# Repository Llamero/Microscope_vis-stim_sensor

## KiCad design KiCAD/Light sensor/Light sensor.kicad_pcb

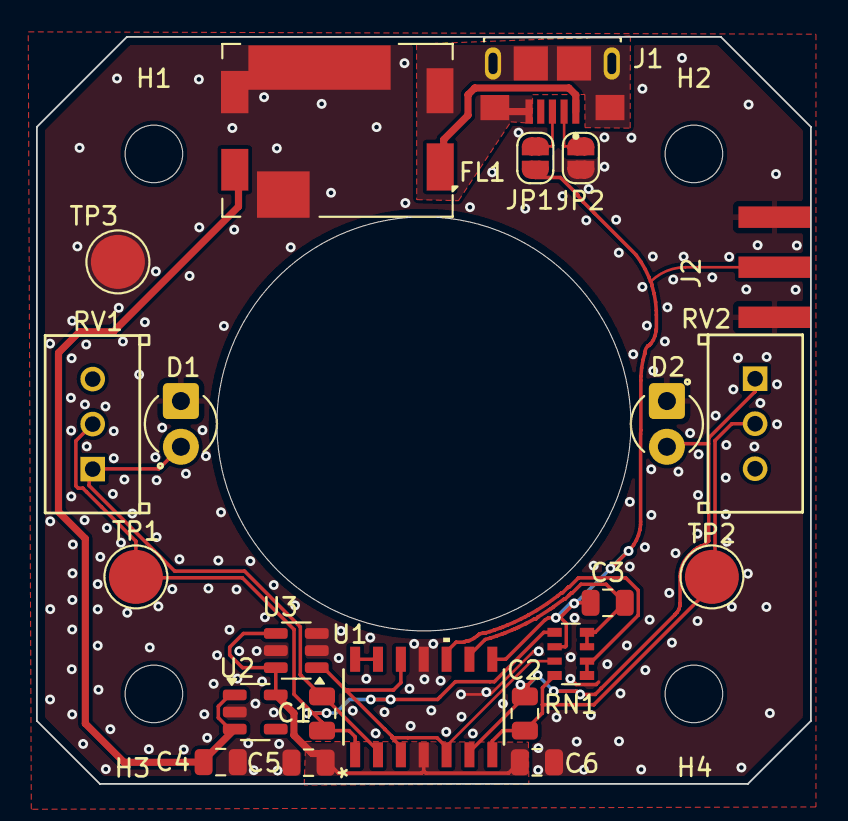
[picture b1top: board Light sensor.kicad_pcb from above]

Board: 2 copper layers, 43.0 x 41.5 mm, 26 parts (0 on the bottom side), 16 nets.

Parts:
C1, C2, C3: 10pF; C_0805_2012Metric
C4, C6: 1µF; C_0805_2012Metric
C5: 100nF; C_0805_2012Metric
D1, D2: D_Photo; XDCR_SFH_229
FL1: BNX025; Filter_Murata_BNX025
H1, H2, H3, H4: MountingHole; MountingHole_3.2mm_M3
J1: USB_B_Micro; AMPHENOL_10118193-0001LF
J2: Conn_Coaxial; ADAMTECH_RF2-143-T-17-50-G
JP1, JP2: Jumper_2_Open; SolderJumper-2_P1.3mm_Open_RoundedPad1.0x1.5mm
RN1: 1k, 10k-10x Gain; R_Array_Convex_4x0603
RV1, RV2: R_Potentiometer_Trim; POT_PV36W_MUR
TP1, TP2, TP3: TestPoint; TestPoint_Pad_D3.0mm
U1: Opamp_Quad; SOIC14_SL_MCH
U2: 3.8V LDO; SOT-23-5
U3: 1.024 Vref; SOT-23-6

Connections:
+1V0: RN1.7 (R2.2), U1.3 (+), U1.5 (+), U1.12 (+), U3.1 (OUT)
+3.8V: C5.1, C6.1, U1.4 (V+), U2.5 (OUT), U3.4 (~SHDN), U3.6 (Vdd)
+5V: C4.1, FL1.2 (CB), U2.1 (IN), U2.3 (EN)
/Vd1: C1.1, RN1.5 (R4.2), RV1.2, TP1.1, U1.1
/Vd2: C2.1, RN1.8 (R1.2), RV2.2, TP2.1, U1.7
/Vout: C3.1, J2.1 (In), JP1.2 (B), RN1.6 (R3.2), U1.8
GND: C4.2, C5.2, C6.2, D1.2 (A), D2.2 (A), FL1.4 (CG), J2.2 (Ext), JP2.2 (B), TP3.1, U1.11 (V-), U2.2 (GND), U3.2 (GND), U3.3 (GND), U3.5 (GND)
unnamed: C1.2, D1.1 (K), RV1.1, U1.2 (-)
unnamed: C2.2, D2.1 (K), RV2.1, U1.6 (-)
unnamed: FL1.1 (B), J1.1 (VBUS)
unnamed: FL1.3 (PSG), J1.5 (GND), J1.6 (Shield)
unnamed: J1.3 (D+), JP1.1 (A)
unnamed: J1.2 (D-), JP2.1 (A)
unnamed: RN1.1 (R1.1), RN1.2 (R2.1), U1.10 (+)
unnamed: C3.2, RN1.3 (R3.1), RN1.4 (R4.1), U1.9 (-)
unnamed: U1.13 (-), U1.14

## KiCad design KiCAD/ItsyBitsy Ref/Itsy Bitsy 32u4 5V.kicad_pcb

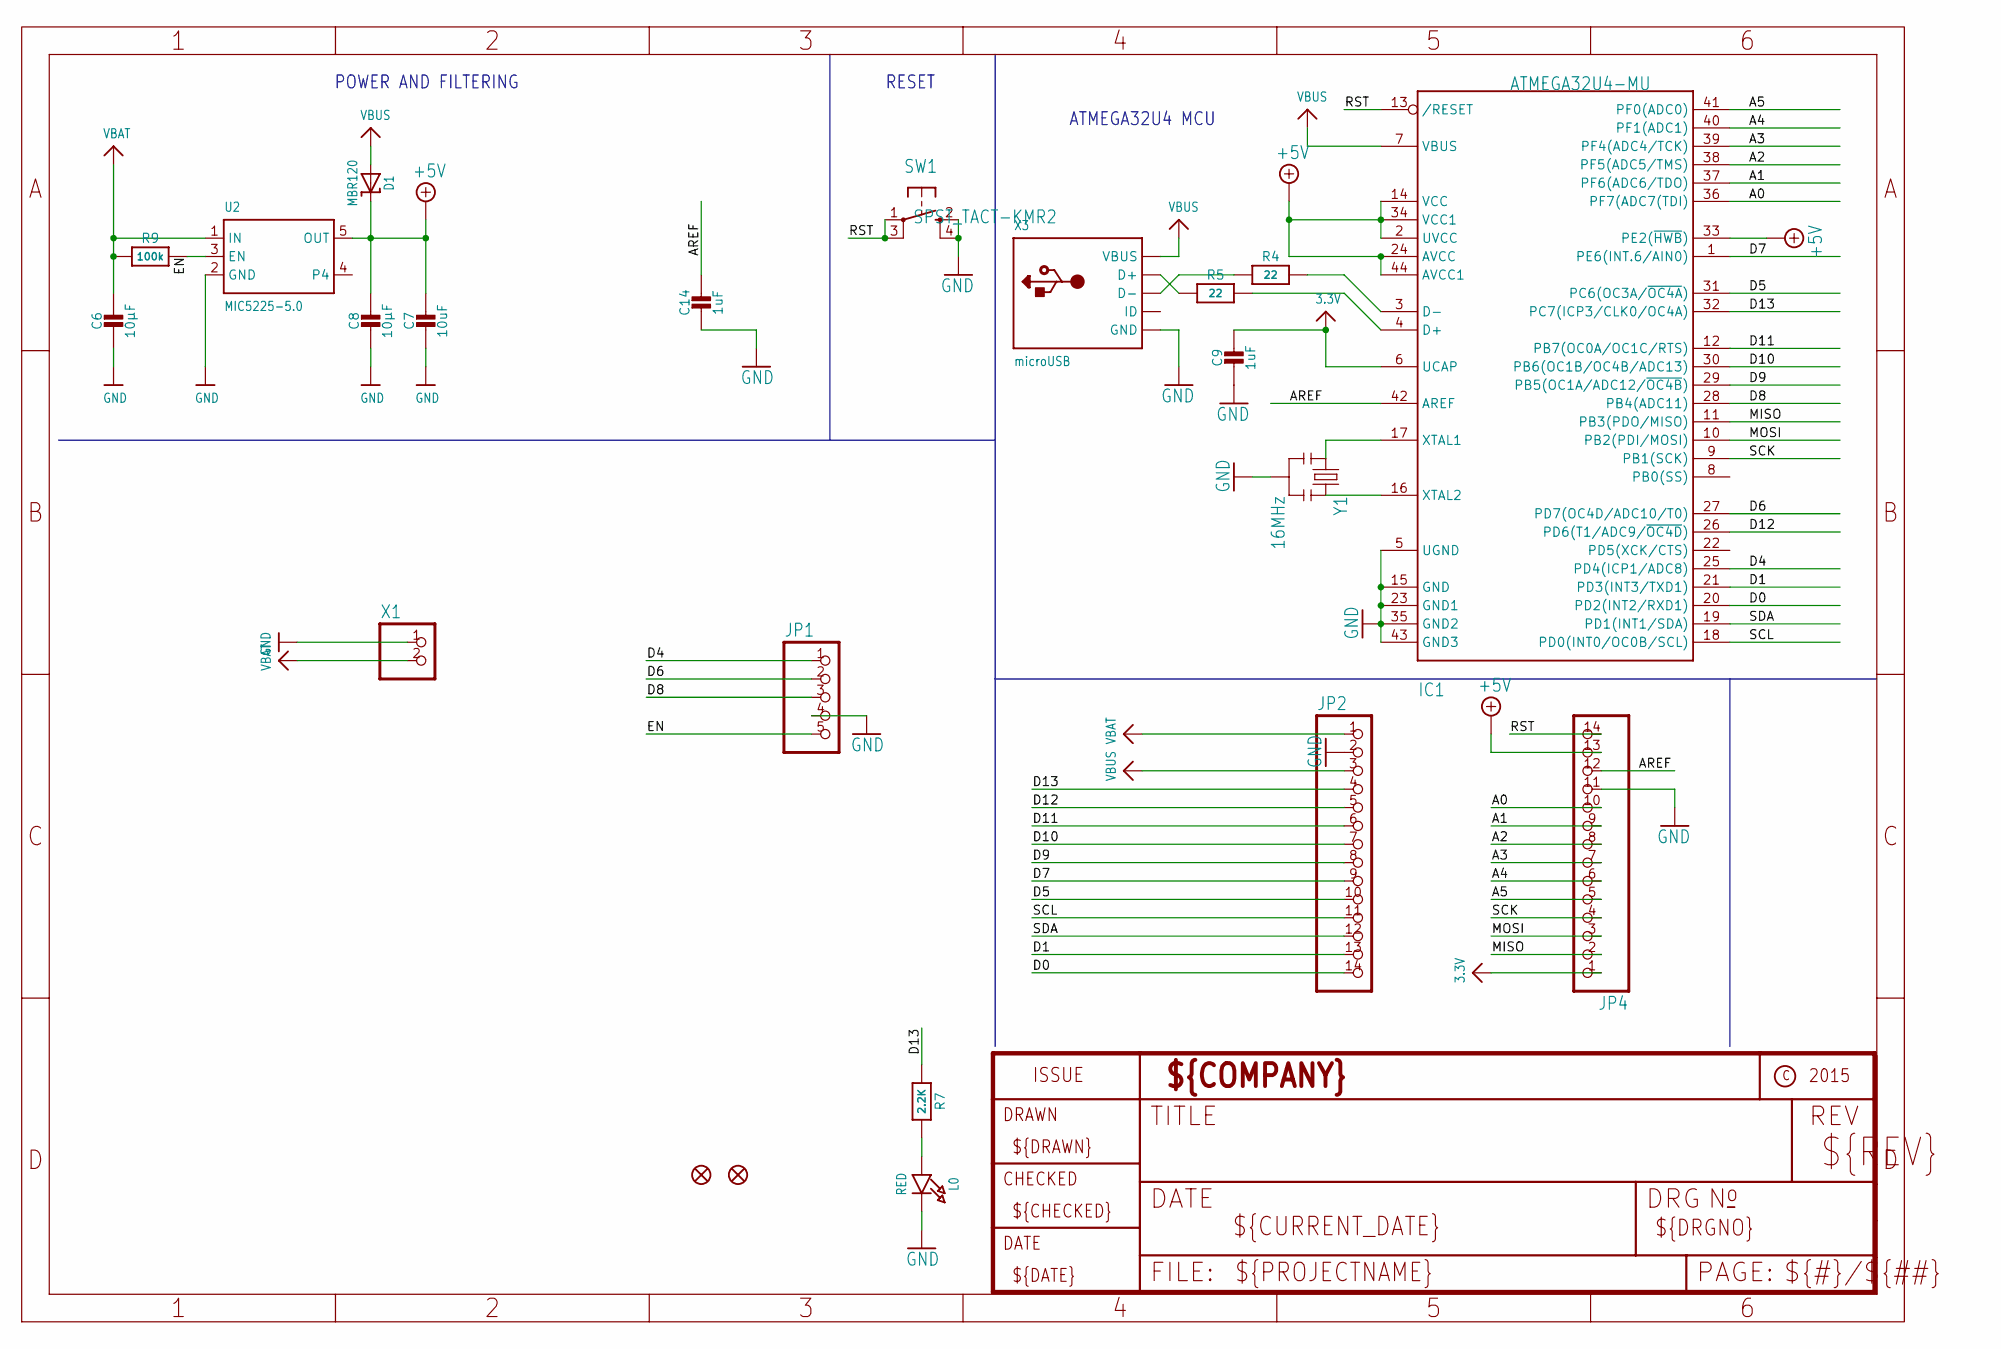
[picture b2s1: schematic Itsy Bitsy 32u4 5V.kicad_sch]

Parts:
C6, C8: 10µF; 0805-NO
C7: 10uF; 0805-NO
C9, C14: 1uF; 0603-NO
D1: MBR120; SOD-123
IC1: ATMEGA32U4-MU; TQFN44_7MM
JP1: HEADER-1X5ROUND; 1X05_ROUND
JP2, JP4: HEADER-1X14; 1X14_ROUND70
L0: RED; CHIPLED_0805_NOOUTLINE
R4, R5: 22; 0603-NO
R7: 2.2K; 0603-NO
R9: 100k; 0603-NO
SW1: SPST_TACT-KMR2; KMR2
U2: MIC5225-5.0; SOT23-5
U$34, U$35: FIDUCIAL""; FIDUCIAL_1MM
X1: CON_JST_PH_2PIN; JSTPH2
X3: microUSB; 4UCONN_20329_V2
Y1: 16MHz; RESONATOR-SMD

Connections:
3.3V: C9.1, IC1.6 (UCAP), JP4.1
+5V: C7.1, C8.1, D1.C, IC1.2 (UVCC), IC1.14 (VCC), IC1.24 (AVCC), IC1.33 (PE2(~HWB)), IC1.34 (VCC1), IC1.44 (AVCC1), JP4.13, U2.5 (OUT)
A0: IC1.36 (PF7(ADC7(TDI)), JP4.10
A1: IC1.37 (PF6(ADC6/TDO)), JP4.9
A2: IC1.38 (PF5(ADC5/TMS)), JP4.8
A3: IC1.39 (PF4(ADC4/TCK)), JP4.7
A4: IC1.40 (PF1(ADC1)), JP4.6
A5: IC1.41 (PF0(ADC0)), JP4.5
AREF: C14.1, IC1.42 (AREF), JP4.12
D0: IC1.20 (PD2(INT2/RXD1)), JP2.14
D1: IC1.21 (PD3(INT3/TXD1)), JP2.13
D4: IC1.25 (PD4(ICP1/ADC8)), JP1.1
D5: IC1.31 (PC6(OC3A/~OC4A)), JP2.10
D6: IC1.27 (PD7(OC4D/ADC10/T0)), JP1.2
D7: IC1.1 (PE6(INT.6/AIN0)), JP2.9
D8: IC1.28 (PB4(ADC11)), JP1.3
D9: IC1.29 (PB5(OC1A/ADC12/~OC4B)), JP2.8
D10: IC1.30 (PB6(OC1B/OC4B/ADC13)), JP2.7
D11: IC1.12 (PB7(OC0A/OC1C/RTS)), JP2.6
D12: IC1.26 (PD6(T1/ADC9/~OC4D)), JP2.5
D13: IC1.32 (PC7(ICP3/CLK0/OC4A)), JP2.4, R7.1
D+: IC1.4 (D+), R5.2
D-: IC1.3 (D-), R4.2
EN: JP1.5, R9.2, U2.3 (EN)
GND: C6.2, C7.2, C8.2, C9.2, C14.2, IC1.5 (UGND), IC1.15 (GND), IC1.23 (GND1), IC1.35 (GND2), IC1.43 (GND3), JP1.4, JP2.2, JP4.11, L0.C, SW1.2 (S), SW1.4 (S1), U2.2 (GND), X1.1, X3.BASE@1 (GND), X3.BASE@2 (GND), X3.GND, X3.SPRT@1 (GND), X3.SPRT@2 (GND), X3.SPRT@3 (GND), X3.SPRT@4 (GND), Y1.2
MISO: IC1.11 (PB3(PDO/MISO)), JP4.2
MOSI: IC1.10 (PB2(PDI/MOSI)), JP4.3
unnamed: L0.A, R7.2
unnamed: IC1.16 (XTAL2), Y1.3
unnamed: IC1.17 (XTAL1), Y1.1
unnamed: R5.1, X3.D+
unnamed: R4.1, X3.D-
RST: IC1.13 (/RESET), JP4.14, SW1.1, SW1.3 (P1)
SCK: IC1.9 (PB1(SCK)), JP4.4
SCL: IC1.18 (PD0(INT0/OC0B/SCL)), JP2.11
SDA: IC1.19 (PD1(INT1/SDA)), JP2.12
VBAT: C6.1, JP2.1, R9.1, U2.1 (IN), X1.2
VBUS: D1.A, IC1.7 (VBUS), JP2.3, X3.VBUS

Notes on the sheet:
POWER AND FILTERING
ATMEGA32U4 MCU
RESET

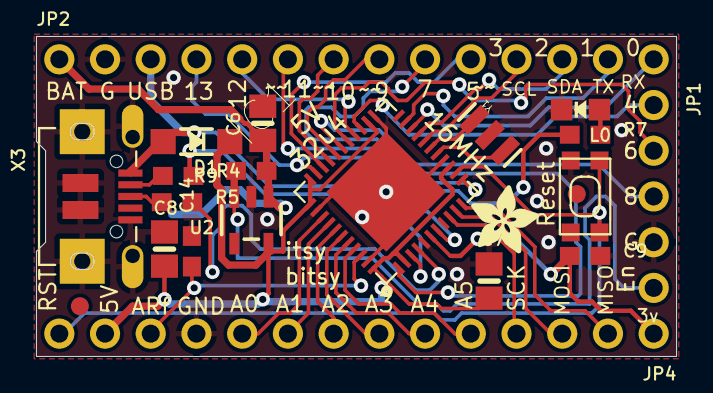
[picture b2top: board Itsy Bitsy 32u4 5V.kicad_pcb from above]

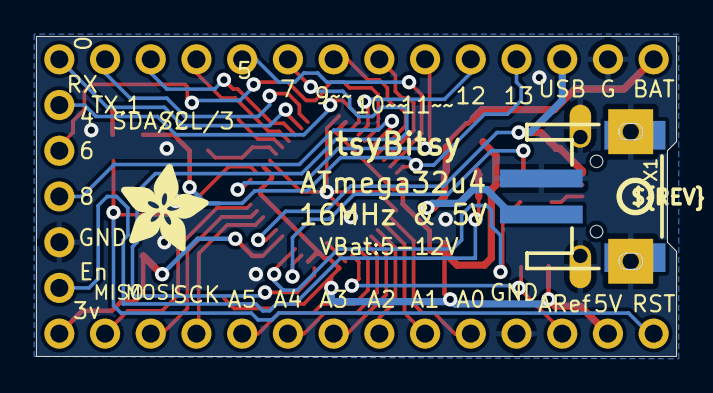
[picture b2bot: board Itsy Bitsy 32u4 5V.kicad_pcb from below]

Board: 2 copper layers, 35.6 x 17.8 mm, 25 parts (3 on the bottom side), 38 nets.

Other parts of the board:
U$4: ADAFRUIT_5MM
U$7: ADAFRUIT_3.5MM
U$10: PCBFEAT-REV-040

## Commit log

2025-05-06 Initial draft
2025-05-07 Add offset to diff amp, swap for better photodiodes
2025-05-07 Add coax connector for Vout
